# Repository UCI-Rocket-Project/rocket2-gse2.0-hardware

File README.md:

# rocket2 Ground Support Electronics (GSE) 
Current version: v2.1  
Documentation is rendered with MKDocs: [Click Here](https://uci-rocket-project.github.io/rocket2-gse2.0-hardware/)  

# CAD

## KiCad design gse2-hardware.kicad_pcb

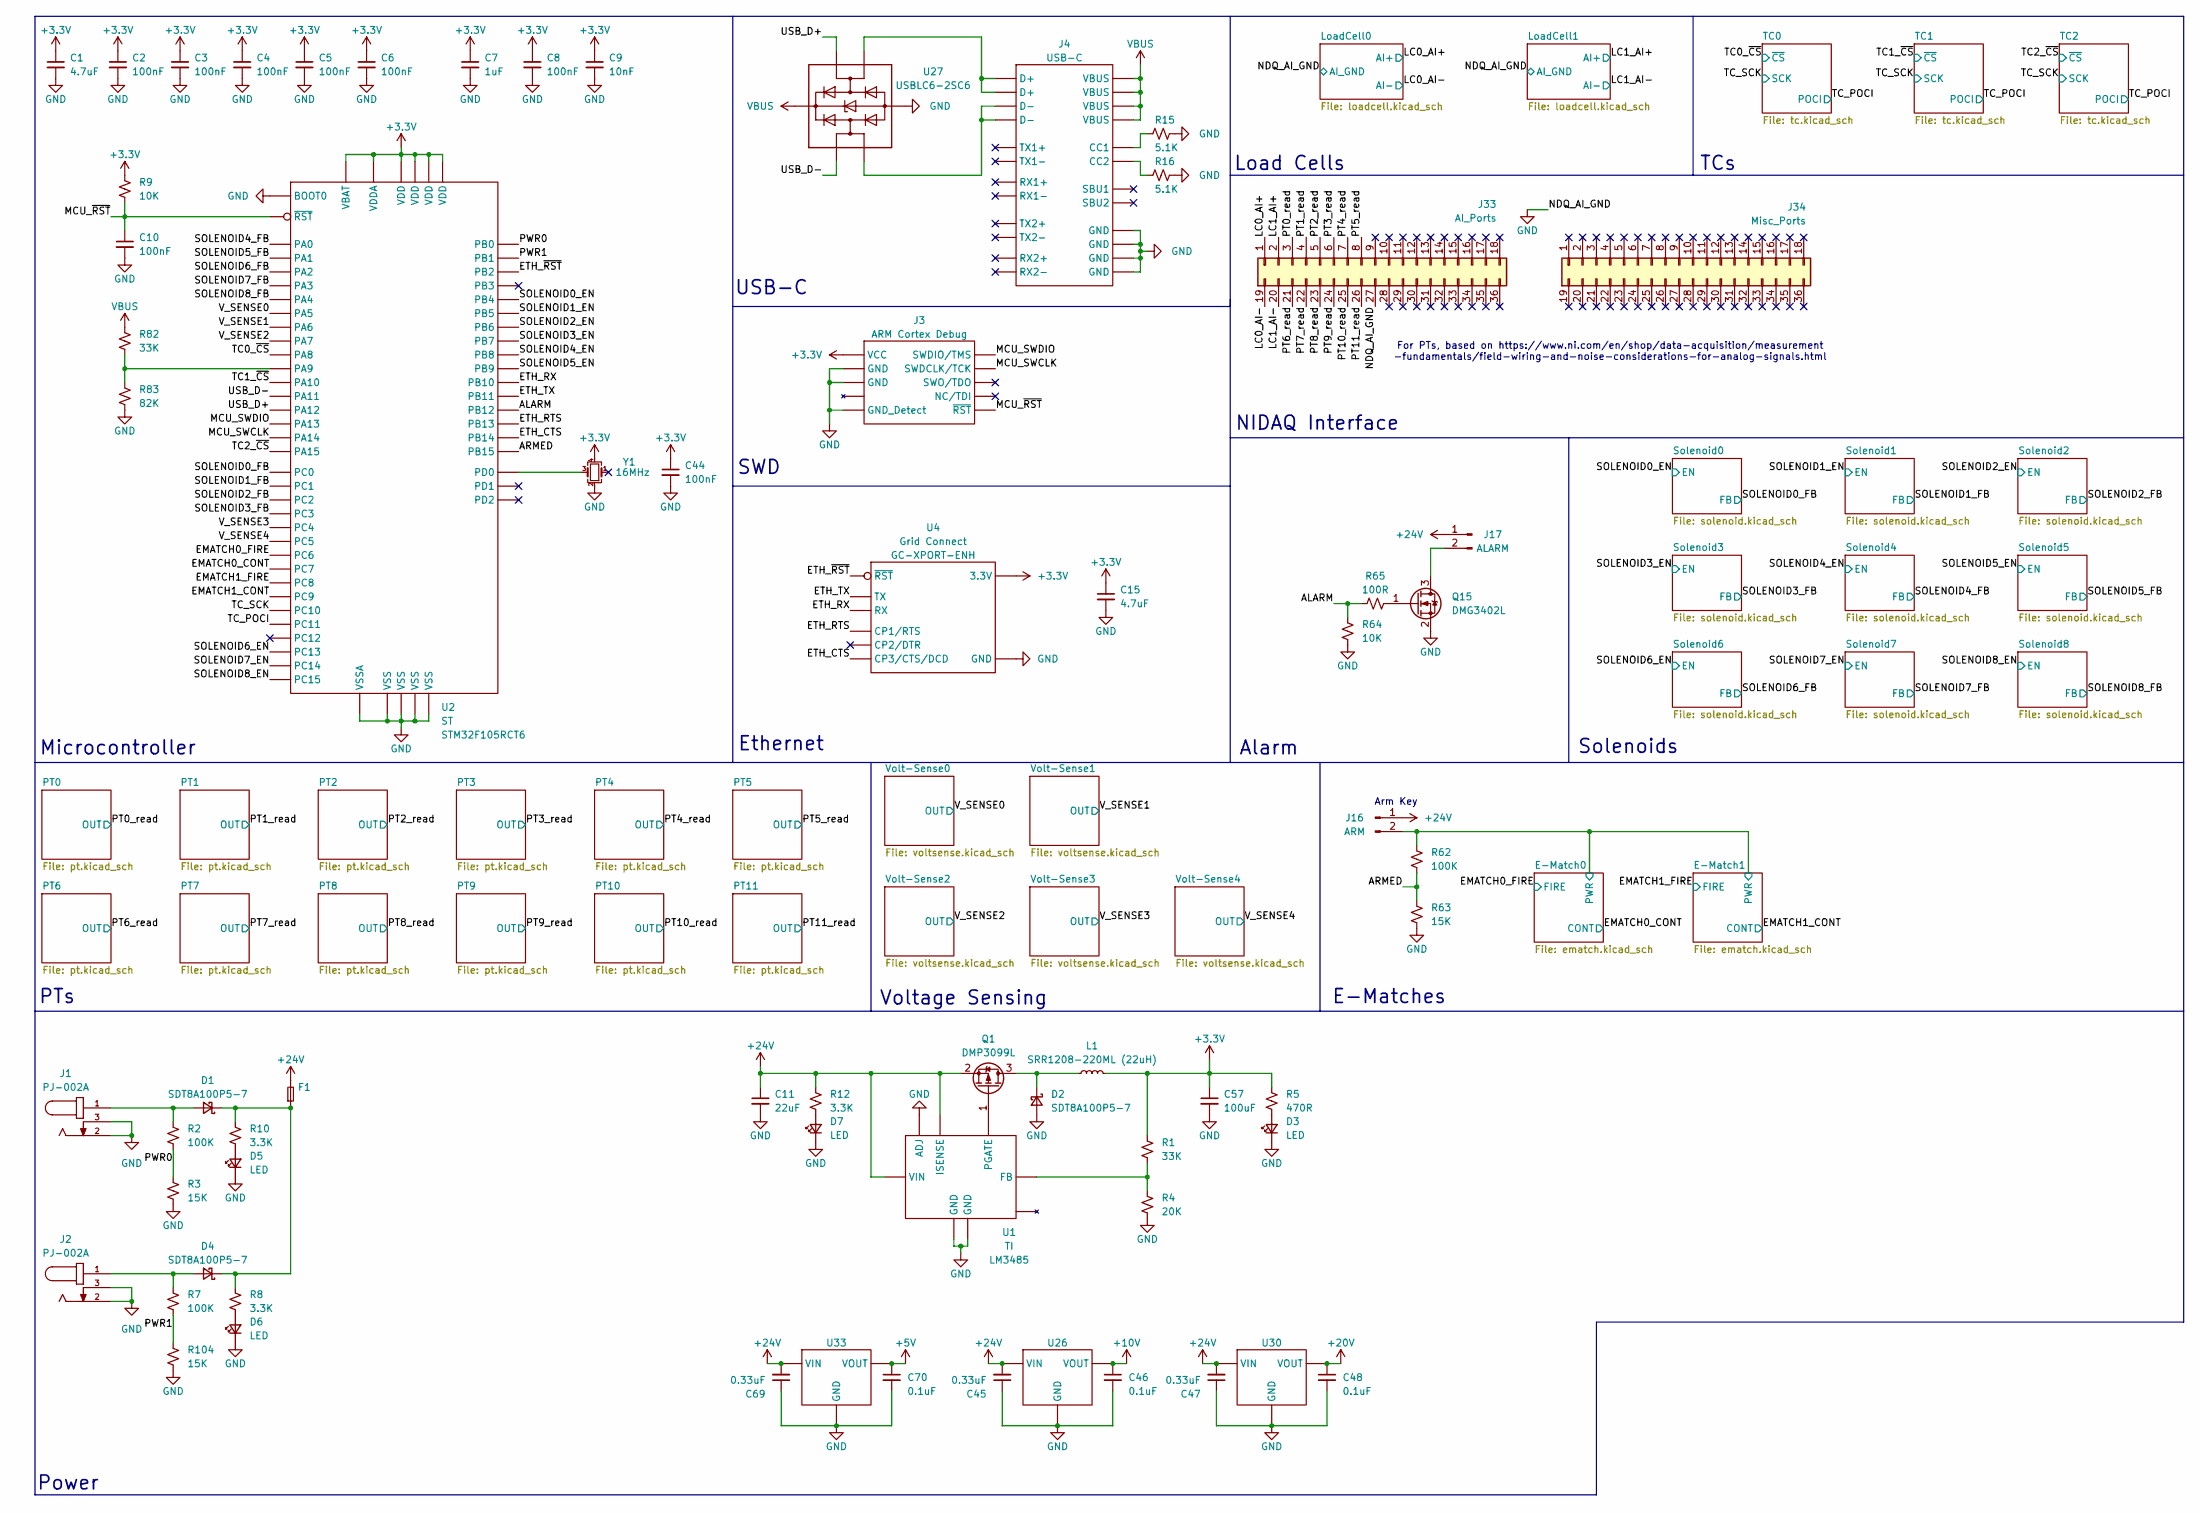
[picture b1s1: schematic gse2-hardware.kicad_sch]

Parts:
C1, C15: 4.7uF; C_0603_1608Metric; Part # Generic 4.7uF 6.3V X7R 0603 MLCC
C2, C3, C4, C5, C6, C8, C10, C44: 100nF; C_0603_1608Metric; Part # Generic 100nF 6.3V X7R 0402 MLCC
C7: 1uF; C_0603_1608Metric; Part # Generic 1uF 6.3V X7R 0402 MLCC
C9: 10nF; C_0603_1608Metric; Part # Generic 10nF 6.3V X7R 0402 MLCC
C11: 22uF; C_0603_1608Metric; Part # Generic 22uF 35V X5R 1206 MLCC
C45, C47, C69: 0.33uF; C_0603_1608Metric; Part # Generic 22uF 35V X5R 1206 MLCC
C46, C48, C70: 0.1uF; C_0603_1608Metric; Part # Generic 22uF 35V X5R 1206 MLCC
C57: 100uF; C_0603_1608Metric; Part # Generic 100uF 6.3V X5R 1206 MLCC
D1, D2, D4: SDT8A100P5-7; D_PowerDI-5; Part # SDT8A100P5-7
D3, D5, D6, D7: LED; LED_0603_1608Metric; Part # Generic Red 0603 LED
F1: Fuseholder_Blade_Mini_Keystone_3568; Part # 3568
J1, J2: PJ-002A; CUI_PJ-002A
J3: ARM Cortex Debug; PinHeader_2x05_P1.27mm_Vertical_SMD; Part # Generic 2x5 1.27mm SMD Pin Header
J4: USB-C; USB_C_Receptacle_GCT_USB4105-xx-A_16P_TopMnt_Horizontal; Part # USB4105-GF-A
J16: ARM; TerminalBlock_MetzConnect_Type055_RT01502HDWU_1x02_P5.00mm_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
J17: ALARM; TerminalBlock_MetzConnect_Type055_RT01502HDWU_1x02_P5.00mm_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
J33: AI_Ports
J34: Misc_Ports
L1: SRR1208-220ML (22uH); L_Bourns_SRR1208_12.7x12.7mm; Part # SRR1208-220ML
Q1: DMP3099L; SOT-23-3; Part # DMP3099L
Q15: DMG3402L; SOT-23-3; Part # DMG3402L
R1, R82: 33K; R_0603_1608Metric; Part # Generic 33K 1% 0402 Resistor
R2, R7, R62: 100K; R_0603_1608Metric; Part # Generic 100K 1% 0402 Resistor
R3, R63, R104: 15K; R_0603_1608Metric; Part # Generic 15K 1% 0402 Resistor
R4: 20K; R_0603_1608Metric; Part # Generic 20K 1% 0402 Resistor
R5: 470R; R_0603_1608Metric; Part # Generic 470R 1% 0402 Resistor
R8, R10, R12: 3.3K; R_0603_1608Metric; Part # Generic 3.3K 1% 0402 Resistor
R9, R64: 10K; R_0603_1608Metric; Part # Generic 10K 1% 0402 Resistor
R15, R16: 5.1K; R_0603_1608Metric; Part # Generic 5.1K 1% 0402 Resistor
R65: 100R; R_0603_1608Metric; Part # Generic 100R 1% 0402 Resistor
R83: 82K; R_0603_1608Metric; Part # Generic 82K 1% 0402 Resistor
U1: VSSOP-8_3x3mm_P0.65mm; Part # LM3485
U2: LQFP-64_10x10mm_P0.5mm; Part # STM32F105RCT6
U4: GC-XPORT; Part # GC-XPORT-ENH
U26: TO-252-2
U27: USBLC6-2SC6; SOT-23-6
U30: TO-252-2; Part # BA78M20FP-E2
U33: SOT-89-3
Y1: 16MHz; Crystal_SMD_2016-4Pin_2.0x1.6mm; Part # ECS-1633-160-BN-TR

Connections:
+3.3V: C1.1, C2.1, C3.1, C4.1, C5.1, C6.1, C7.1, C8.1, C9.1, C15.1, C44.1, C57.1, J3.1 (VCC), L1.2, R1.2, R5.2, R9.2, U2.1 (VBAT), U2.13 (VDDA), U2.19 (VDD), U2.32 (VDD), U2.48 (VDD), U2.64 (VDD), U4.2 (3.3V), Y1.4; also elsewhere on the board
+5V: C70.1, U33.3 (VOUT); also elsewhere on the board
+10V: C46.1, U26.3 (VOUT); also elsewhere on the board
+20V: C48.1, U30.3 (VOUT); also elsewhere on the board
+24V: C11.1, C45.2, C47.2, C69.2, F1.2, J16.1, J17.1, Q1.2 (S), R12.2, U1.1 (ISENSE), U1.8 (VIN), U26.1 (VIN), U30.1 (VIN), U33.1 (VIN); also elsewhere on the board
/ALARM: R64.2, R65.1, U2.33 (PB12)
/ARMED: R62.1, R63.2, U2.36 (PB15)
/E-Match0/PWR: J16.2, R62.2; also elsewhere on the board
/EMATCH0_CONT: U2.38 (PC7); also elsewhere on the board
/EMATCH0_FIRE: U2.37 (PC6); also elsewhere on the board
/EMATCH1_CONT: U2.40 (PC9); also elsewhere on the board
/EMATCH1_FIRE: U2.39 (PC8); also elsewhere on the board
/ETH_CTS: U2.35 (PB14), U4.8 (CP3/CTS/DCD)
/ETH_RTS: U2.34 (PB13), U4.6 (CP1/RTS)
/ETH_RX: U2.29 (PB10), U4.5 (RX)
/ETH_TX: U2.30 (PB11), U4.4 (TX)
/ETH_~RST: U2.28 (PB2), U4.3 (~RST)
/MCU_SWCLK: J3.4 (SWDCLK/TCK), U2.49 (PA14)
/MCU_SWDIO: J3.2 (SWDIO/TMS), U2.46 (PA13)
/MCU_~RST: C10.1, J3.10 (~RST), R9.1, U2.7 (~RST)
/PWR0: R2.1, R3.2, U2.26 (PB0)
/PWR1: R7.1, R104.2, U2.27 (PB1)
/SOLENOID0_EN: U2.56 (PB4); also elsewhere on the board
/SOLENOID0_FB: U2.8 (PC0); also elsewhere on the board
/SOLENOID1_EN: U2.57 (PB5); also elsewhere on the board
/SOLENOID1_FB: U2.9 (PC1); also elsewhere on the board
/SOLENOID2_EN: U2.58 (PB6); also elsewhere on the board
/SOLENOID2_FB: U2.10 (PC2); also elsewhere on the board
/SOLENOID3_EN: U2.59 (PB7); also elsewhere on the board
/SOLENOID3_FB: U2.11 (PC3); also elsewhere on the board
/SOLENOID4_EN: U2.61 (PB8); also elsewhere on the board
/SOLENOID4_FB: U2.14 (PA0); also elsewhere on the board
/SOLENOID5_EN: U2.62 (PB9); also elsewhere on the board
/SOLENOID5_FB: U2.15 (PA1); also elsewhere on the board
/SOLENOID6_EN: U2.2 (PC13); also elsewhere on the board
/SOLENOID6_FB: U2.16 (PA2); also elsewhere on the board
/SOLENOID7_EN: U2.3 (PC14); also elsewhere on the board
/SOLENOID7_FB: U2.17 (PA3); also elsewhere on the board
/SOLENOID8_EN: U2.4 (PC15); also elsewhere on the board
/SOLENOID8_FB: U2.20 (PA4); also elsewhere on the board
/TC0_~CS: U2.50 (PA15); also elsewhere on the board
/TC1_~CS: U2.43 (PA10); also elsewhere on the board
/TC2_~CS: U2.41 (PA8); also elsewhere on the board
/TC_POCI: U2.52 (PC11); also elsewhere on the board
/TC_SCK: U2.51 (PC10); also elsewhere on the board
/USB_D+: U2.45 (PA12), U27.4 (I/O2)
/USB_D-: U2.44 (PA11), U27.6 (I/O1)
/V_SENSE0: U2.21 (PA5); also elsewhere on the board
/V_SENSE1: U2.22 (PA6); also elsewhere on the board
/V_SENSE2: U2.23 (PA7); also elsewhere on the board
/V_SENSE3: U2.24 (PC4); also elsewhere on the board
/V_SENSE4: U2.25 (PC5); also elsewhere on the board
GND: C1.2, C2.2, C3.2, C4.2, C5.2, C6.2, C7.2, C8.2, C9.2, C10.2, C11.2, C15.2, C44.2, C45.1, C46.2, C47.1, C48.2, C57.2, C69.1, C70.2, D2.2 (A), D3.1 (K), D5.1 (K), D6.1 (K), D7.1 (K), J1.2, J1.3, J2.2, J2.3, J3.3 (GND), J3.5 (GND), J3.9 (GND_Detect), J4.A1 (GND), J4.A12 (GND), J4.B1 (GND), J4.B12 (GND), J33.27, Q15.2 (S), R3.1, R4.1, R15.1, R16.1, R63.1, R64.1, R83.1, R104.1, U1.2 (GND), U1.5 (ADJ), U1.6 (GND), U2.12 (VSSA), U2.18 (VSS), U2.31 (VSS), U2.47 (VSS), U2.60 (BOOT0), U2.63 (VSS), U4.1 (GND), U26.2 (GND), U27.2 (GND), U30.2 (GND), U33.2 (GND), Y1.2; also elsewhere on the board
unnamed: D1.2 (A), J1.1, R2.2
unnamed: D1.1 (K), D4.1 (K), F1.1, R8.2, R10.2
unnamed: D2.1 (K), L1.1, Q1.3 (D)
unnamed: D3.2 (A), R5.1
unnamed: D4.2 (A), J2.1, R7.2
unnamed: D5.2 (A), R10.1
unnamed: D6.2 (A), R8.1
unnamed: D7.2 (A), R12.1
unnamed: J4.A5 (CC1), R15.2
unnamed: J4.B5 (CC2), R16.2
unnamed: J4.A6 (D+), J4.B6 (D+), U27.3 (I/O2)
unnamed: J4.A7 (D-), J4.B7 (D-), U27.1 (I/O1)
unnamed: J17.2, Q15.3 (D)
unnamed: Q1.1 (G), U1.7 (PGATE)
unnamed: Q15.1 (G), R65.2
unnamed: R1.1, R4.2, U1.4 (FB)
unnamed: R82.1, R83.2, U2.42 (PA9)
unnamed: U2.5 (PD0), Y1.3
VBUS: J4.A4 (VBUS), J4.A9 (VBUS), J4.B4 (VBUS), J4.B9 (VBUS), R82.2, U27.5 (VBUS)

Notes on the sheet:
TCs
Microcontroller
E-Matches
SWD
Ethernet
PTs
Load Cells
Arm Key
Solenoids
Power
Voltage Sensing
For PTs, based on https://www.ni.com/en/shop/data-acquisition/measurement -fundamentals/field-wiring-and-noise-considerations-for-analog-signals.html
Alarm
USB-C
NIDAQ Interface

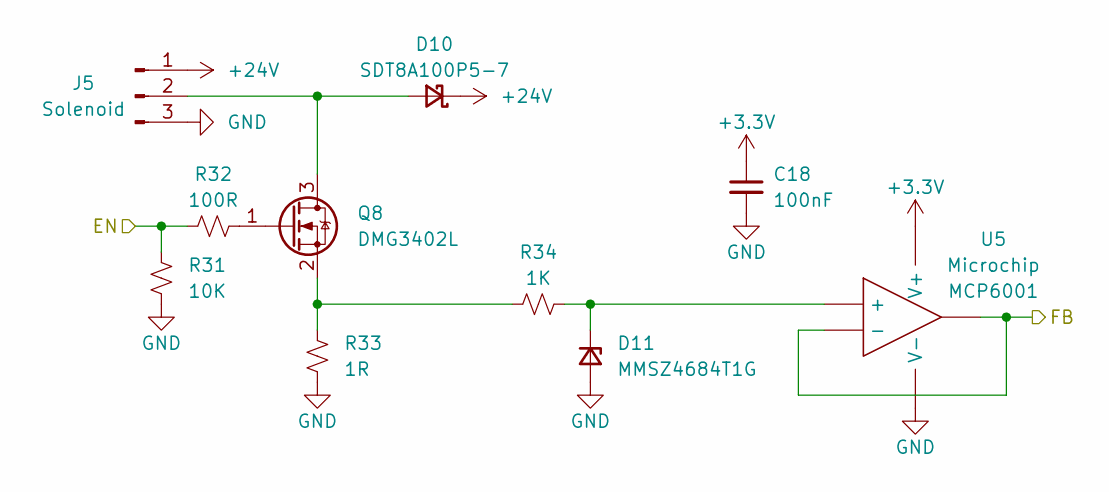
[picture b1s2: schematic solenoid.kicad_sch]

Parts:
C18: 100nF; C_0603_1608Metric; Part # Generic 100nF 6.3V X7R 0402 MLCC
D10: SDT8A100P5-7; D_PowerDI-5; Part # SDT8A100P5-7
D11: MMSZ4684T1G; D_SOD-123; Part # MMSZ4684T1G
J5: Solenoid; GX-16 3 pin
Q8: DMG3402L; SOT-23-3; Part # DMG3402L
R31: 10K; R_0603_1608Metric; Part # Generic 10K 1% 0402 Resistor
R32: 100R; R_0603_1608Metric; Part # Generic 100R 1% 0402 Resistor
R33: 1R; R_0603_1608Metric; Part # Generic 1R 2W 1% 2512 Resistor
R34: 1K; R_0603_1608Metric; Part # Generic 1K 1% 0402 Resistor
U5: SOT-23-5; Part # MCP6001

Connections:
+3.3V: C18.1, U5.5 (V+); also elsewhere on the board
+24V: D10.1 (K), J5.1; also elsewhere on the board
/SOLENOID0_EN: R31.2, R32.1; also elsewhere on the board
/SOLENOID0_FB: U5.1, U5.4 (-); also elsewhere on the board
GND: C18.2, D11.2 (A), J5.3, R31.1, R33.1, U5.2 (V-); also elsewhere on the board
unnamed: D10.2 (A), J5.2, Q8.3 (D)
unnamed: D11.1 (K), R34.2, U5.3 (+)
unnamed: Q8.1 (G), R32.2
unnamed: Q8.2 (S), R33.2, R34.1

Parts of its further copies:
C12, C13, C14, C16, C17, C19, C20, C21: 100nF; C_0603_1608Metric; Part # Generic 100nF 6.3V X7R 0402 MLCC
D8, D12, D14, D16, D18, D20, D22, D24: SDT8A100P5-7; D_PowerDI-5; Part # SDT8A100P5-7
D9, D13, D15, D17, D19, D21, D23, D25: MMSZ4684T1G; D_SOD-123; Part # MMSZ4684T1G
J6, J7, J8, J10, J11, J12, J13, J39: Solenoid; GX-16 3 pin
Q2, Q3, Q4, Q5, Q6, Q7, Q9, Q10: DMG3402L; SOT-23-3; Part # DMG3402L
R11, R18, R22, R26, R30, R38, R42, R46: 10K; R_0603_1608Metric; Part # Generic 10K 1% 0402 Resistor
R13, R19, R23, R27, R35, R39, R43, R47: 100R; R_0603_1608Metric; Part # Generic 100R 1% 0402 Resistor
R14, R20, R24, R28, R36, R40, R44, R48: 1R; R_0603_1608Metric; Part # Generic 1R 2W 1% 2512 Resistor
R17, R21, R25, R29, R37, R41, R45, R49: 1K; R_0603_1608Metric; Part # Generic 1K 1% 0402 Resistor
U3, U6, U7, U8, U9, U10, U11, U12: SOT-23-5; Part # MCP6001

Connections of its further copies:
+3.3V: C12.1, C13.1, C14.1, C16.1, C17.1, C19.1, C20.1, C21.1, U3.5 (V+), U6.5 (V+), U7.5 (V+), U8.5 (V+), U9.5 (V+), U10.5 (V+), U11.5 (V+), U12.5 (V+); also elsewhere on the board
+24V: D8.1 (K), D12.1 (K), D14.1 (K), D16.1 (K), D18.1 (K), D20.1 (K), D22.1 (K), D24.1 (K), J6.1, J7.1, J8.1, J10.1, J11.1, J12.1, J13.1, J39.1; also elsewhere on the board
/SOLENOID1_EN: R11.2, R13.1; also elsewhere on the board
/SOLENOID1_FB: U3.1, U3.4 (-); also elsewhere on the board
/SOLENOID2_EN: R18.2, R19.1; also elsewhere on the board
/SOLENOID2_FB: U6.1, U6.4 (-); also elsewhere on the board
/SOLENOID3_EN: R22.2, R23.1; also elsewhere on the board
/SOLENOID3_FB: U7.1, U7.4 (-); also elsewhere on the board
/SOLENOID4_EN: R26.2, R27.1; also elsewhere on the board
/SOLENOID4_FB: U8.1, U8.4 (-); also elsewhere on the board
/SOLENOID5_EN: R30.2, R35.1; also elsewhere on the board
/SOLENOID5_FB: U9.1, U9.4 (-); also elsewhere on the board
/SOLENOID6_EN: R38.2, R39.1; also elsewhere on the board
/SOLENOID6_FB: U10.1, U10.4 (-); also elsewhere on the board
/SOLENOID7_EN: R42.2, R43.1; also elsewhere on the board
/SOLENOID7_FB: U11.1, U11.4 (-); also elsewhere on the board
/SOLENOID8_EN: R46.2, R47.1; also elsewhere on the board
/SOLENOID8_FB: U12.1, U12.4 (-); also elsewhere on the board
GND: C12.2, C13.2, C14.2, C16.2, C17.2, C19.2, C20.2, C21.2, D9.2 (A), D13.2 (A), D15.2 (A), D17.2 (A), D19.2 (A), D21.2 (A), D23.2 (A), D25.2 (A), J6.3, J7.3, J8.3, J10.3, J11.3, J12.3, J13.3, J39.3, R11.1, R14.1, R18.1, R20.1, R22.1, R24.1, R26.1, R28.1, R30.1, R36.1, R38.1, R40.1, R42.1, R44.1, R46.1, R48.1, U3.2 (V-), U6.2 (V-), U7.2 (V-), U8.2 (V-), U9.2 (V-), U10.2 (V-), U11.2 (V-), U12.2 (V-); also elsewhere on the board
unnamed: D8.2 (A), J6.2, Q2.3 (D)
unnamed: D9.1 (K), R17.2, U3.3 (+)
unnamed: D12.2 (A), J7.2, Q3.3 (D)
unnamed: D13.1 (K), R21.2, U6.3 (+)
unnamed: D14.2 (A), J8.2, Q4.3 (D)
unnamed: D15.1 (K), R25.2, U7.3 (+)
unnamed: D16.2 (A), J10.2, Q5.3 (D)
unnamed: D17.1 (K), R29.2, U8.3 (+)
unnamed: D18.2 (A), J11.2, Q6.3 (D)
unnamed: D19.1 (K), R37.2, U9.3 (+)
unnamed: D20.2 (A), J12.2, Q7.3 (D)
unnamed: D21.1 (K), R41.2, U10.3 (+)
unnamed: D22.2 (A), J13.2, Q9.3 (D)
unnamed: D23.1 (K), R45.2, U11.3 (+)
unnamed: D24.2 (A), J39.2, Q10.3 (D)
unnamed: D25.1 (K), R49.2, U12.3 (+)
unnamed: Q2.1 (G), R13.2
unnamed: Q2.2 (S), R14.2, R17.1
unnamed: Q3.1 (G), R19.2
unnamed: Q3.2 (S), R20.2, R21.1
unnamed: Q4.1 (G), R23.2
unnamed: Q4.2 (S), R24.2, R25.1
unnamed: Q5.1 (G), R27.2
unnamed: Q5.2 (S), R28.2, R29.1
unnamed: Q6.1 (G), R35.2
unnamed: Q6.2 (S), R36.2, R37.1
unnamed: Q7.1 (G), R39.2
unnamed: Q7.2 (S), R40.2, R41.1
unnamed: Q9.1 (G), R43.2
unnamed: Q9.2 (S), R44.2, R45.1
unnamed: Q10.1 (G), R47.2
unnamed: Q10.2 (S), R48.2, R49.1

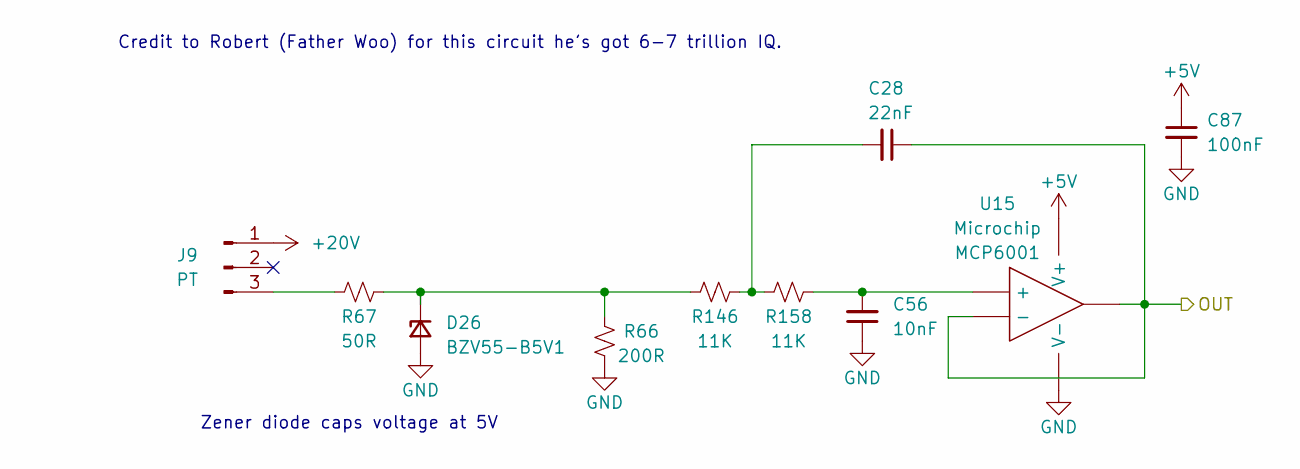
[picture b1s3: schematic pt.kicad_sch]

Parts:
C28: 22nF; C_0603_1608Metric; Part # Generic 100nF 6.3V X7R 0402 MLCC
C56: 10nF; C_0603_1608Metric; Part # Generic 100nF 6.3V X7R 0402 MLCC
C87: 100nF; C_0603_1608Metric; Part # Generic 100nF 6.3V X7R 0402 MLCC
D26: BZV55-B5V1; D_MiniMELF; Part # BZV55-B5V1
J9: PT; GX-12 3 pin
R66: 200R; R_0603_1608Metric; Part # Generic 1K 1% 0402 Resistor
R67: 50R; R_0603_1608Metric
R146, R158: 11K; R_0603_1608Metric; Part # Generic 1K 1% 0402 Resistor
U15: SOT-23-5; Part # MCP6001

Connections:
+5V: C87.1, U15.5 (V+); also elsewhere on the board
+20V: J9.1; also elsewhere on the board
/PT0_read: C28.1, U15.1, U15.4 (-)
GND: C56.1, C87.2, D26.2 (A), R66.1, U15.2 (V-); also elsewhere on the board
unnamed: C28.2, R146.1, R158.2
unnamed: D26.1 (K), R66.2, R67.1, R146.2
unnamed: J9.3, R67.2
unnamed: C56.2, R158.1, U15.3 (+)

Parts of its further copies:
C29, C30, C31, C34, C35, C36, C37, C38, C39, C40, C41: 22nF; C_0603_1608Metric; Part # Generic 100nF 6.3V X7R 0402 MLCC
C88, C89, C90, C91, C92, C93, C94, C95, C96, C97, C98: 100nF; C_0603_1608Metric; Part # Generic 100nF 6.3V X7R 0402 MLCC
C99, C100, C110, C111, C112, C113, C114, C115, C116, C117, C118: 10nF; C_0603_1608Metric; Part # Generic 100nF 6.3V X7R 0402 MLCC
D27, D28, D29, D30, D31, D32, D33, D34, D35, D36, D37: BZV55-B5V1; D_MiniMELF; Part # BZV55-B5V1
J19, J20, J21, J22, J23, J24, J25, J26, J27, J28, J29: PT; GX-12 3 pin
R68, R70, R72, R74, R76, R78, R80, R84, R86, R88, R90: 50R; R_0603_1608Metric
R69, R71, R73, R75, R77, R79, R81, R85, R87, R89, R91: 200R; R_0603_1608Metric; Part # Generic 1K 1% 0402 Resistor
R147, R148, R149, R150, R151, R152, R153, R154, R155, R156, R157, R159, R160, R161, R162, R163, R164, R165, R166, R167, R168, R169: 11K; R_0603_1608Metric; Part # Generic 1K 1% 0402 Resistor
U16, U17, U18, U20, U21, U22, U23, U24, U25, U28, U29: SOT-23-5; Part # MCP6001

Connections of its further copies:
+5V: C88.1, C89.1, C90.1, C91.1, C92.1, C93.1, C94.1, C95.1, C96.1, C97.1, C98.1, U16.5 (V+), U17.5 (V+), U18.5 (V+), U20.5 (V+), U21.5 (V+), U22.5 (V+), U23.5 (V+), U24.5 (V+), U25.5 (V+), U28.5 (V+), U29.5 (V+); also elsewhere on the board
+20V: J19.1, J20.1, J21.1, J22.1, J23.1, J24.1, J25.1, J26.1, J27.1, J28.1, J29.1; also elsewhere on the board
/PT1_read: C29.1, U16.1, U16.4 (-)
/PT2_read: C30.1, U17.1, U17.4 (-)
/PT3_read: C31.1, U18.1, U18.4 (-)
/PT4_read: C34.1, U20.1, U20.4 (-)
/PT5_read: C35.1, U21.1, U21.4 (-)
/PT6_read: C36.1, U22.1, U22.4 (-)
/PT7_read: C37.1, U23.1, U23.4 (-)
/PT8_read: C38.1, U24.1, U24.4 (-)
/PT9_read: C39.1, U25.1, U25.4 (-)
/PT10_read: C40.1, U28.1, U28.4 (-)
/PT11_read: C41.1, U29.1, U29.4 (-)
GND: C88.2, C89.2, C90.2, C91.2, C92.2, C93.2, C94.2, C95.2, C96.2, C97.2, C98.2, C99.1, C100.1, C110.1, C111.1, C112.1, C113.1, C114.1, C115.1, C116.1, C117.1, C118.1, D27.2 (A), D28.2 (A), D29.2 (A), D30.2 (A), D31.2 (A), D32.2 (A), D33.2 (A), D34.2 (A), D35.2 (A), D36.2 (A), D37.2 (A), R69.1, R71.1, R73.1, R75.1, R77.1, R79.1, R81.1, R85.1, R87.1, R89.1, R91.1, U16.2 (V-), U17.2 (V-), U18.2 (V-), U20.2 (V-), U21.2 (V-), U22.2 (V-), U23.2 (V-), U24.2 (V-), U25.2 (V-), U28.2 (V-), U29.2 (V-); also elsewhere on the board
unnamed: C29.2, R147.1, R159.2
unnamed: C30.2, R148.1, R160.2
unnamed: C31.2, R149.1, R161.2
unnamed: C34.2, R150.1, R162.2
unnamed: C35.2, R151.1, R163.2
unnamed: C36.2, R152.1, R164.2
unnamed: C37.2, R153.1, R165.2
unnamed: C38.2, R154.1, R166.2
unnamed: C39.2, R155.1, R167.2
unnamed: C40.2, R156.1, R168.2
unnamed: C41.2, R157.1, R169.2
unnamed: D27.1 (K), R68.1, R69.2, R147.2
unnamed: D28.1 (K), R70.1, R71.2, R148.2
unnamed: D29.1 (K), R72.1, R73.2, R149.2
unnamed: D30.1 (K), R74.1, R75.2, R150.2
unnamed: D31.1 (K), R76.1, R77.2, R151.2
unnamed: D32.1 (K), R78.1, R79.2, R152.2
unnamed: D33.1 (K), R80.1, R81.2, R153.2
unnamed: D34.1 (K), R84.1, R85.2, R154.2
unnamed: D35.1 (K), R86.1, R87.2, R155.2
unnamed: D36.1 (K), R88.1, R89.2, R156.2
unnamed: D37.1 (K), R90.1, R91.2, R157.2
unnamed: J19.3, R68.2
unnamed: J20.3, R70.2
unnamed: J21.3, R72.2
unnamed: J22.3, R74.2
unnamed: J23.3, R76.2
unnamed: J24.3, R78.2
unnamed: J25.3, R80.2
unnamed: J26.3, R84.2
unnamed: J27.3, R86.2
unnamed: J28.3, R88.2
unnamed: J29.3, R90.2
unnamed: C99.2, R159.1, U16.3 (+)
unnamed: C100.2, R160.1, U17.3 (+)
unnamed: C110.2, R161.1, U18.3 (+)
unnamed: C111.2, R162.1, U20.3 (+)
unnamed: C112.2, R163.1, U21.3 (+)
unnamed: C113.2, R164.1, U22.3 (+)
unnamed: C114.2, R165.1, U23.3 (+)
unnamed: C115.2, R166.1, U24.3 (+)
unnamed: C116.2, R167.1, U25.3 (+)
unnamed: C117.2, R168.1, U28.3 (+)
unnamed: C118.2, R169.1, U29.3 (+)

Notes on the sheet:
Zener diode caps voltage at 5V
Credit to Robert (Father Woo) for this circuit he's got 6-7 trillion IQ.

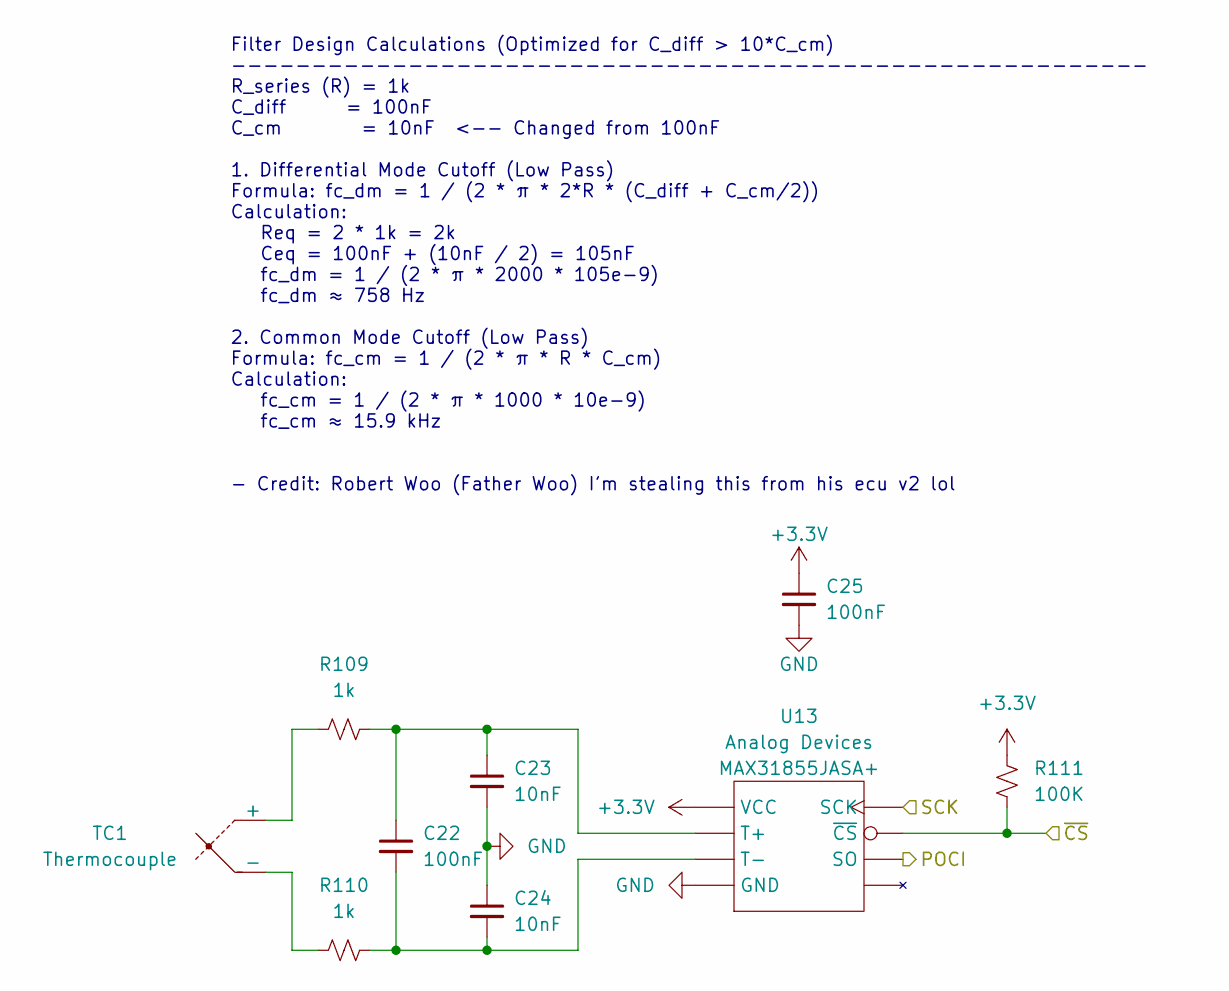
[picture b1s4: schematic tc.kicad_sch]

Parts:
C22, C25: 100nF; C_0603_1608Metric; Part # Generic CAP CER 0.1UF 6.3V X7R 0402
C23, C24: 10nF; C_0603_1608Metric; Part # Generic CAP CER 10NF 6.3V X7R 0402
R109, R110: 1k; R_0603_1608Metric; Part # Generic RES SMD 1K OHM 1% 1/16W 0402
R111: 100K; R_0603_1608Metric; Part # Generic RES SMD 100K OHM 1% 1/16W 0402
TC1: Thermocouple; AM-K-PCB; Part # AM-K-PCB
U13: SOIC-8_3.9x4.9mm_P1.27mm; Part # MAX31855JASA+

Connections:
+3.3V: C25.1, R111.1, U13.4 (VCC); also elsewhere on the board
/TC0_~CS: R111.2, U13.6 (~CS); also elsewhere on the board
/TC_POCI: U13.7 (SO); also elsewhere on the board
/TC_SCK: U13.5 (SCK); also elsewhere on the board
GND: C23.2, C24.1, C25.2, U13.1 (GND); also elsewhere on the board
unnamed: R109.1, TC1.1 (+)
unnamed: R110.1, TC1.2 (-)
unnamed: C22.1, C23.1, R109.2, U13.3 (T+)
unnamed: C22.2, C24.2, R110.2, U13.2 (T-)

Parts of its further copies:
C32, C64, C65, C68: 100nF; C_0603_1608Metric; Part # Generic CAP CER 0.1UF 6.3V X7R 0402
C33, C63, C66, C67: 10nF; C_0603_1608Metric; Part # Generic CAP CER 10NF 6.3V X7R 0402
R112, R113, R115, R116: 1k; R_0603_1608Metric; Part # Generic RES SMD 1K OHM 1% 1/16W 0402
R114, R117: 100K; R_0603_1608Metric; Part # Generic RES SMD 100K OHM 1% 1/16W 0402
TC2, TC3: Thermocouple; AM-K-PCB; Part # AM-K-PCB
U14, U19: SOIC-8_3.9x4.9mm_P1.27mm; Part # MAX31855JASA+

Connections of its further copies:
+3.3V: C64.1, C68.1, R114.1, R117.1, U14.4 (VCC), U19.4 (VCC); also elsewhere on the board
/TC1_~CS: R114.2, U14.6 (~CS); also elsewhere on the board
/TC2_~CS: R117.2, U19.6 (~CS); also elsewhere on the board
/TC_POCI: U14.7 (SO), U19.7 (SO); also elsewhere on the board
/TC_SCK: U14.5 (SCK), U19.5 (SCK); also elsewhere on the board
GND: C33.2, C63.1, C64.2, C66.2, C67.1, C68.2, U14.1 (GND), U19.1 (GND); also elsewhere on the board
unnamed: R112.1, TC2.1 (+)
unnamed: R113.1, TC2.2 (-)
unnamed: R115.1, TC3.1 (+)
unnamed: R116.1, TC3.2 (-)
unnamed: C32.1, C33.1, R112.2, U14.3 (T+)
unnamed: C32.2, C63.2, R113.2, U14.2 (T-)
unnamed: C65.1, C66.1, R115.2, U19.3 (T+)
unnamed: C65.2, C67.2, R116.2, U19.2 (T-)

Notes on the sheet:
Filter Design Calculations (Optimized for C_diff > 10*C_cm) --------------------------------------------------------- R_series (R) = 1k C_diff = 100nF C_cm = 10nF <-- Changed from 100nF 1. Differential Mode Cutoff (Low Pass) Formula: fc_dm = 1 / (2 * π * 2*R * (C_diff + C_cm/2)) Calculation: Req = 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

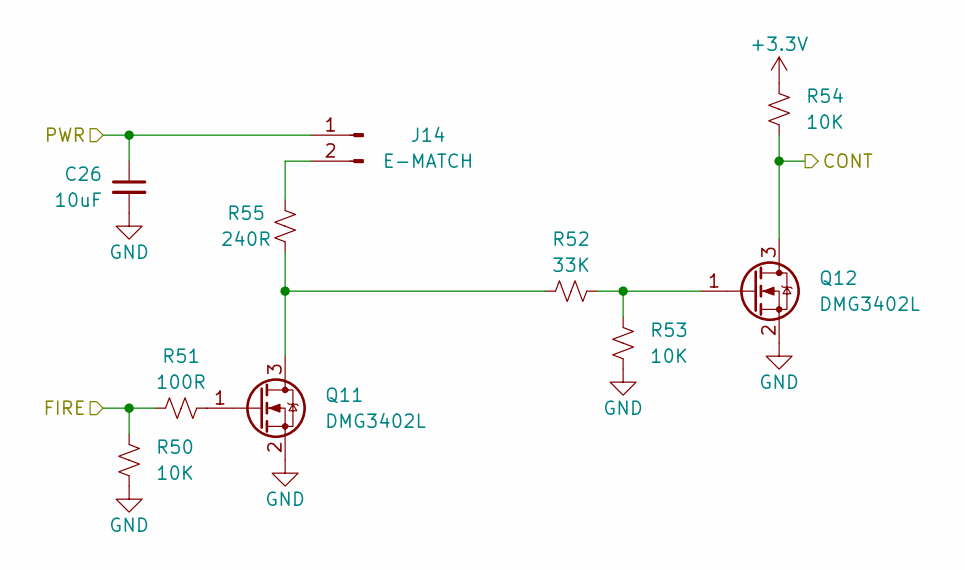
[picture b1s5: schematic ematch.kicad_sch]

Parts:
C26: 10uF; C_0603_1608Metric; Part # Generic 10uF 35V X5R 1206 MLCC
J14: E-MATCH; TerminalBlock_MetzConnect_Type055_RT01502HDWU_1x02_P5.00mm_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
Q11, Q12: DMG3402L; SOT-23-3; Part # DMG3402L
R50, R53, R54: 10K; R_0603_1608Metric; Part # Generic 10K 1% 0402 Resistor
R51: 100R; R_0603_1608Metric; Part # Generic 100R 1% 0402 Resistor
R52: 33K; R_0603_1608Metric; Part # Generic 33K 1% 0402 Resistor
R55: 240R; R_0603_1608Metric; Part # Generic 33K 1% 0402 Resistor

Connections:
+3.3V: R54.2; also elsewhere on the board
/E-Match0/PWR: C26.1, J14.1; also elsewhere on the board
/EMATCH0_CONT: Q12.3 (D), R54.1; also elsewhere on the board
/EMATCH0_FIRE: R50.2, R51.1; also elsewhere on the board
GND: C26.2, Q11.2 (S), Q12.2 (S), R50.1, R53.1; also elsewhere on the board
unnamed: J14.2, R55.2
unnamed: Q11.3 (D), R52.1, R55.1
unnamed: Q11.1 (G), R51.2
unnamed: Q12.1 (G), R52.2, R53.2

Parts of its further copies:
C27: 10uF; C_0603_1608Metric; Part # Generic 10uF 35V X5R 1206 MLCC
J15: E-MATCH; TerminalBlock_MetzConnect_Type055_RT01502HDWU_1x02_P5.00mm_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
Q13, Q14: DMG3402L; SOT-23-3; Part # DMG3402L
R56, R60, R61: 10K; R_0603_1608Metric; Part # Generic 10K 1% 0402 Resistor
R57: 100R; R_0603_1608Metric; Part # Generic 100R 1% 0402 Resistor
R58: 240R; R_0603_1608Metric; Part # Generic 33K 1% 0402 Resistor
R59: 33K; R_0603_1608Metric; Part # Generic 33K 1% 0402 Resistor

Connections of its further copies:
+3.3V: R61.2; also elsewhere on the board
/E-Match0/PWR: C27.1, J15.1; also elsewhere on the board
/EMATCH1_CONT: Q14.3 (D), R61.1; also elsewhere on the board
/EMATCH1_FIRE: R56.2, R57.1; also elsewhere on the board
GND: C27.2, Q13.2 (S), Q14.2 (S), R56.1, R60.1; also elsewhere on the board
unnamed: J15.2, R58.2
unnamed: Q13.3 (D), R58.1, R59.1
unnamed: Q13.1 (G), R57.2
unnamed: Q14.1 (G), R59.2, R60.2

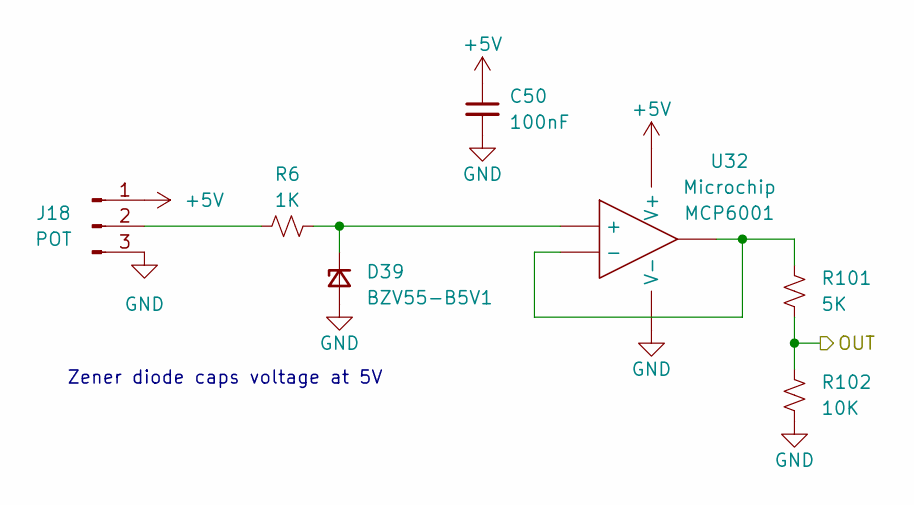
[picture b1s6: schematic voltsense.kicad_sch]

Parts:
C50: 100nF; C_0603_1608Metric; Part # Generic 100nF 6.3V X7R 0402 MLCC
D39: BZV55-B5V1; D_MiniMELF; Part # BZV55-B5V1
J18: POT; GX-12 3 pin
R6: 1K; R_0603_1608Metric; Part # Generic 1K 1% 0402 Resistor
R101: 5K; R_0603_1608Metric; Part # Generic 5K 1% 0402 Resistor
R102: 10K; R_0603_1608Metric; Part # Generic 10K 1% 0402 Resistor
U32: SOT-23-5; Part # MCP6001

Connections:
+5V: C50.1, J18.1, U32.5 (V+); also elsewhere on the board
/V_SENSE4: R101.1, R102.2; also elsewhere on the board
GND: C50.2, D39.2 (A), J18.3, R102.1, U32.2 (V-); also elsewhere on the board
unnamed: D39.1 (K), R6.2, U32.3 (+)
unnamed: J18.2, R6.1
unnamed: R101.2, U32.1, U32.4 (-)

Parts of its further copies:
C51, C58, C59, C60: 100nF; C_0603_1608Metric; Part # Generic 100nF 6.3V X7R 0402 MLCC
D40, D41, D46, D47: BZV55-B5V1; D_MiniMELF; Part # BZV55-B5V1
J32, J36, J37, J38: POT; GX-12 3 pin
R103, R107, R120, R123: 1K; R_0603_1608Metric; Part # Generic 1K 1% 0402 Resistor
R105, R118, R121, R124: 5K; R_0603_1608Metric; Part # Generic 5K 1% 0402 Resistor
R106, R119, R122, R125: 10K; R_0603_1608Metric; Part # Generic 10K 1% 0402 Resistor
U34, U35, U37, U39: SOT-23-5; Part # MCP6001

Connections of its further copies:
+5V: C51.1, C58.1, C59.1, C60.1, J32.1, J36.1, J37.1, J38.1, U34.5 (V+), U35.5 (V+), U37.5 (V+), U39.5 (V+); also elsewhere on the board
/V_SENSE0: R118.1, R119.2; also elsewhere on the board
/V_SENSE1: R105.1, R106.2; also elsewhere on the board
/V_SENSE2: R121.1, R122.2; also elsewhere on the board
/V_SENSE3: R124.1, R125.2; also elsewhere on the board
GND: C51.2, C58.2, C59.2, C60.2, D40.2 (A), D41.2 (A), D46.2 (A), D47.2 (A), J32.3, J36.3, J37.3, J38.3, R106.1, R119.1, R122.1, R125.1, U34.2 (V-), U35.2 (V-), U37.2 (V-), U39.2 (V-); also elsewhere on the board
unnamed: D40.1 (K), R103.2, U34.3 (+)
unnamed: D41.1 (K), R107.2, U35.3 (+)
unnamed: D46.1 (K), R120.2, U37.3 (+)
unnamed: D47.1 (K), R123.2, U39.3 (+)
unnamed: J32.2, R103.1
unnamed: J36.2, R107.1
unnamed: J37.2, R120.1
unnamed: J38.2, R123.1
unnamed: R105.2, U34.1, U34.4 (-)
unnamed: R118.2, U35.1, U35.4 (-)
unnamed: R121.2, U37.1, U37.4 (-)
unnamed: R124.2, U39.1, U39.4 (-)

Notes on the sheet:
Zener diode caps voltage at 5V

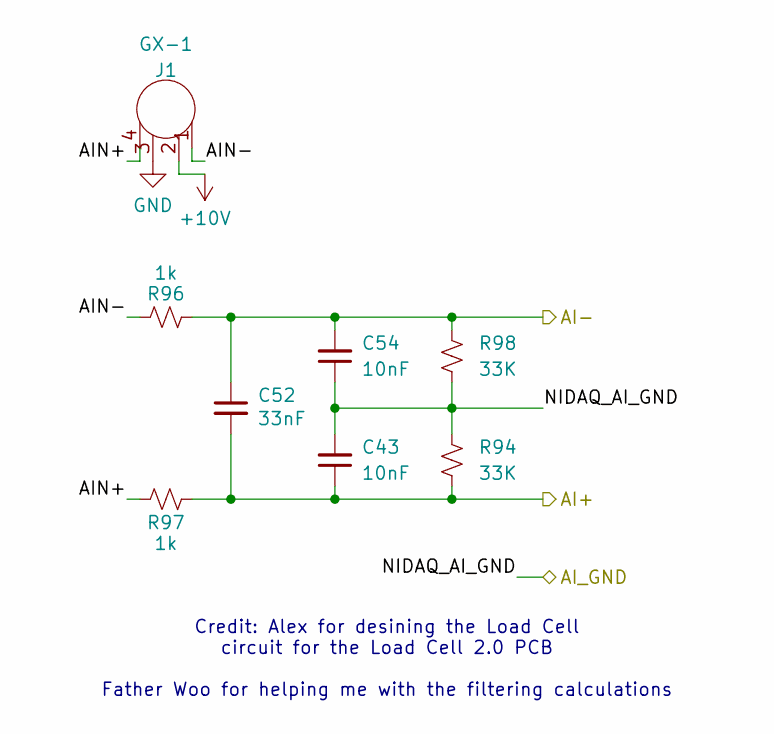
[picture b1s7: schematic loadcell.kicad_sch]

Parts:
C43, C54: 10nF; C_0603_1608Metric
C52: 33nF; C_0603_1608Metric
GX-1: J1; GX16-4
R94, R98: 33K; R_0603_1608Metric; Part # Generic 33K 1% 0402 Resistor
R96, R97: 1k; R_0603_1608Metric

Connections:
+10V: GX-1.2; also elsewhere on the board
/LC0_AI+: C43.1, C52.2, R94.1, R97.2
/LC0_AI-: C52.1, C54.2, R96.1, R98.2
/LoadCell0/AIN+: GX-1.4, R97.1
/LoadCell0/AIN-: GX-1.1, R96.2
GND: C43.2, C54.1, GX-1.3, R94.2, R98.1; also elsewhere on the board

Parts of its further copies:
C42: 33nF; C_0603_1608Metric
C49, C62: 10nF; C_0603_1608Metric
GX-2: J1; GX16-4
R92, R93: 1k; R_0603_1608Metric
R95, R99: 33K; R_0603_1608Metric; Part # Generic 33K 1% 0402 Resistor

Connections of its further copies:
+10V: GX-2.2; also elsewhere on the board
/LC1_AI+: C42.2, C49.1, R93.2, R95.1
/LC1_AI-: C42.1, C62.2, R92.1, R99.2
/LoadCell1/AIN+: GX-2.4, R93.1
/LoadCell1/AIN-: GX-2.1, R92.2
GND: C49.2, C62.1, GX-2.3, R95.2, R99.1; also elsewhere on the board

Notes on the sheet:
Credit: Alex for desining the Load Cell circuit for the Load Cell 2.0 PCB Father Woo for helping me with the filtering calculations

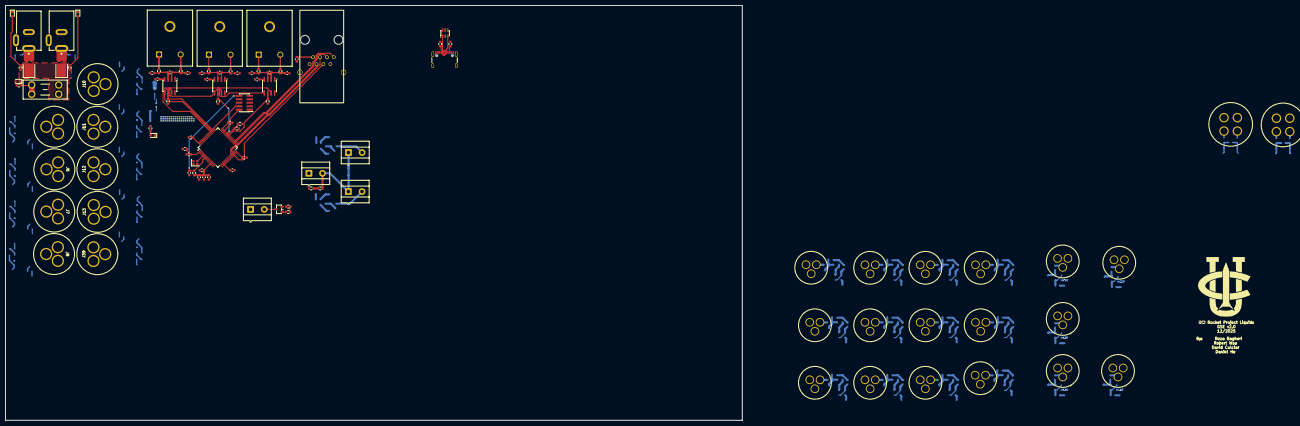
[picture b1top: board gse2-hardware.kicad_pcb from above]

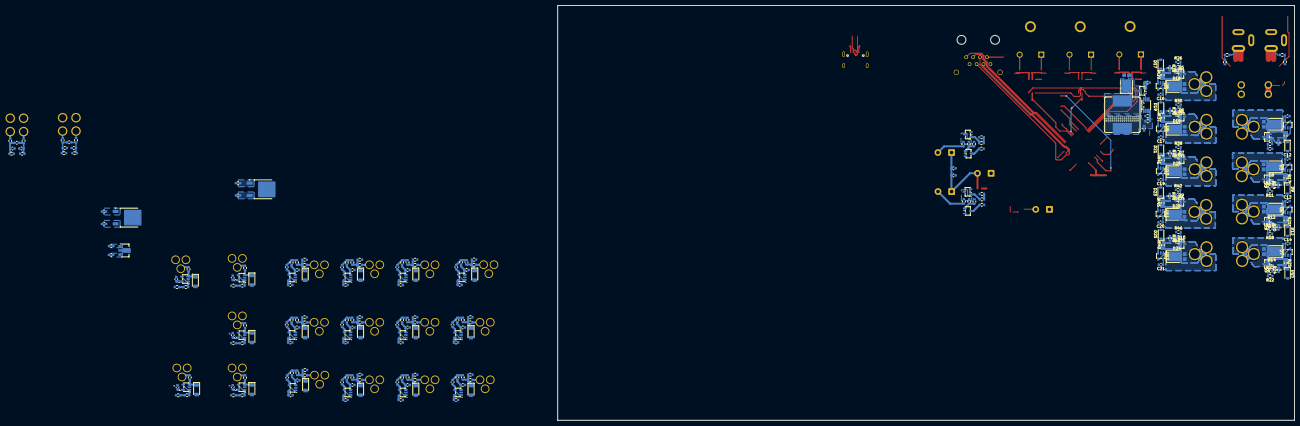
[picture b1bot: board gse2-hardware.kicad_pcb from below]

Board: 4 copper layers, 270.0 x 152.0 mm, 372 parts (272 on the bottom side), 211 nets.
